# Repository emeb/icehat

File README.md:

# icehat

icehat is a small (Zero-sized) RPi hat which comprises a Lattice iCE40 Ultra
FPGA type ice5LP4K-SG48 along with voltage regulators, status LEDs and three
Digilent-style PMOD connectors.

This repository includes the full KiCAD board design source as well as C source
for an RPi user application which can configure the FPGA via GPIO and SPI ports
as well as communicate with a simple SPI slave hosted on the FPGA. Verilog
source for the FPGA test design is also included.

For more info on this project, please see the web page at:

http://ebrombaugh.studionebula.com/embedded/icehat/index.html

Credits: 

Portions of the KiCAD design are based on the RPi_Hat_Template from
xesscorp: https://github.com/xesscorp/RPi_Hat_Template

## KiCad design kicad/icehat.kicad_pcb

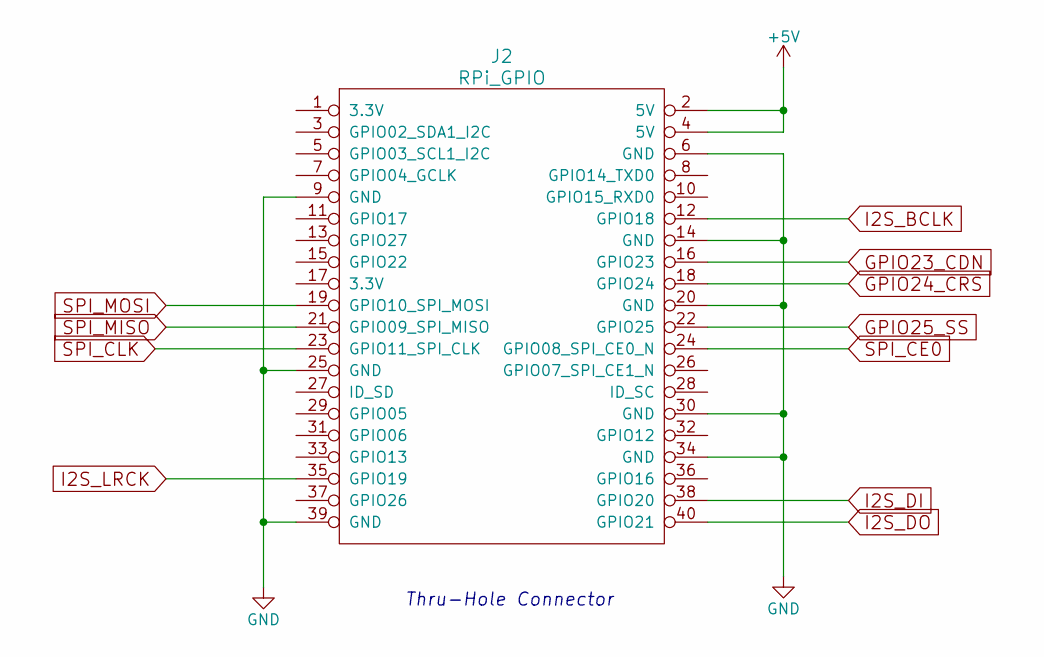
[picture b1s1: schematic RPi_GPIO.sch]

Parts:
J2: RPi_GPIO; Pin_Header_Straight_2x20

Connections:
+5V: J2.2 (5V), J2.4 (5V); also elsewhere on the board
GND: J2.6 (GND), J2.9 (GND), J2.14 (GND), J2.20 (GND), J2.25 (GND), J2.30 (GND), J2.34 (GND), J2.39 (GND); also elsewhere on the board
GPIO23_CDN: J2.16 (GPIO23); also elsewhere on the board
GPIO24_CRS: J2.18 (GPIO24); also elsewhere on the board
GPIO25_SS: J2.22 (GPIO25); also elsewhere on the board
I2S_BCLK: J2.12 (GPIO18); also elsewhere on the board
I2S_DI: J2.38 (GPIO20); also elsewhere on the board
I2S_DO: J2.40 (GPIO21); also elsewhere on the board
I2S_LRCK: J2.35 (GPIO19); also elsewhere on the board
SPI_CE0: J2.24 (GPIO08_SPI_CE0_N); also elsewhere on the board
SPI_CLK: J2.23 (GPIO11_SPI_CLK); also elsewhere on the board
SPI_MISO: J2.21 (GPIO09_SPI_MISO); also elsewhere on the board
SPI_MOSI: J2.19 (GPIO10_SPI_MOSI); also elsewhere on the board

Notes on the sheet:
Thru-Hole Connector

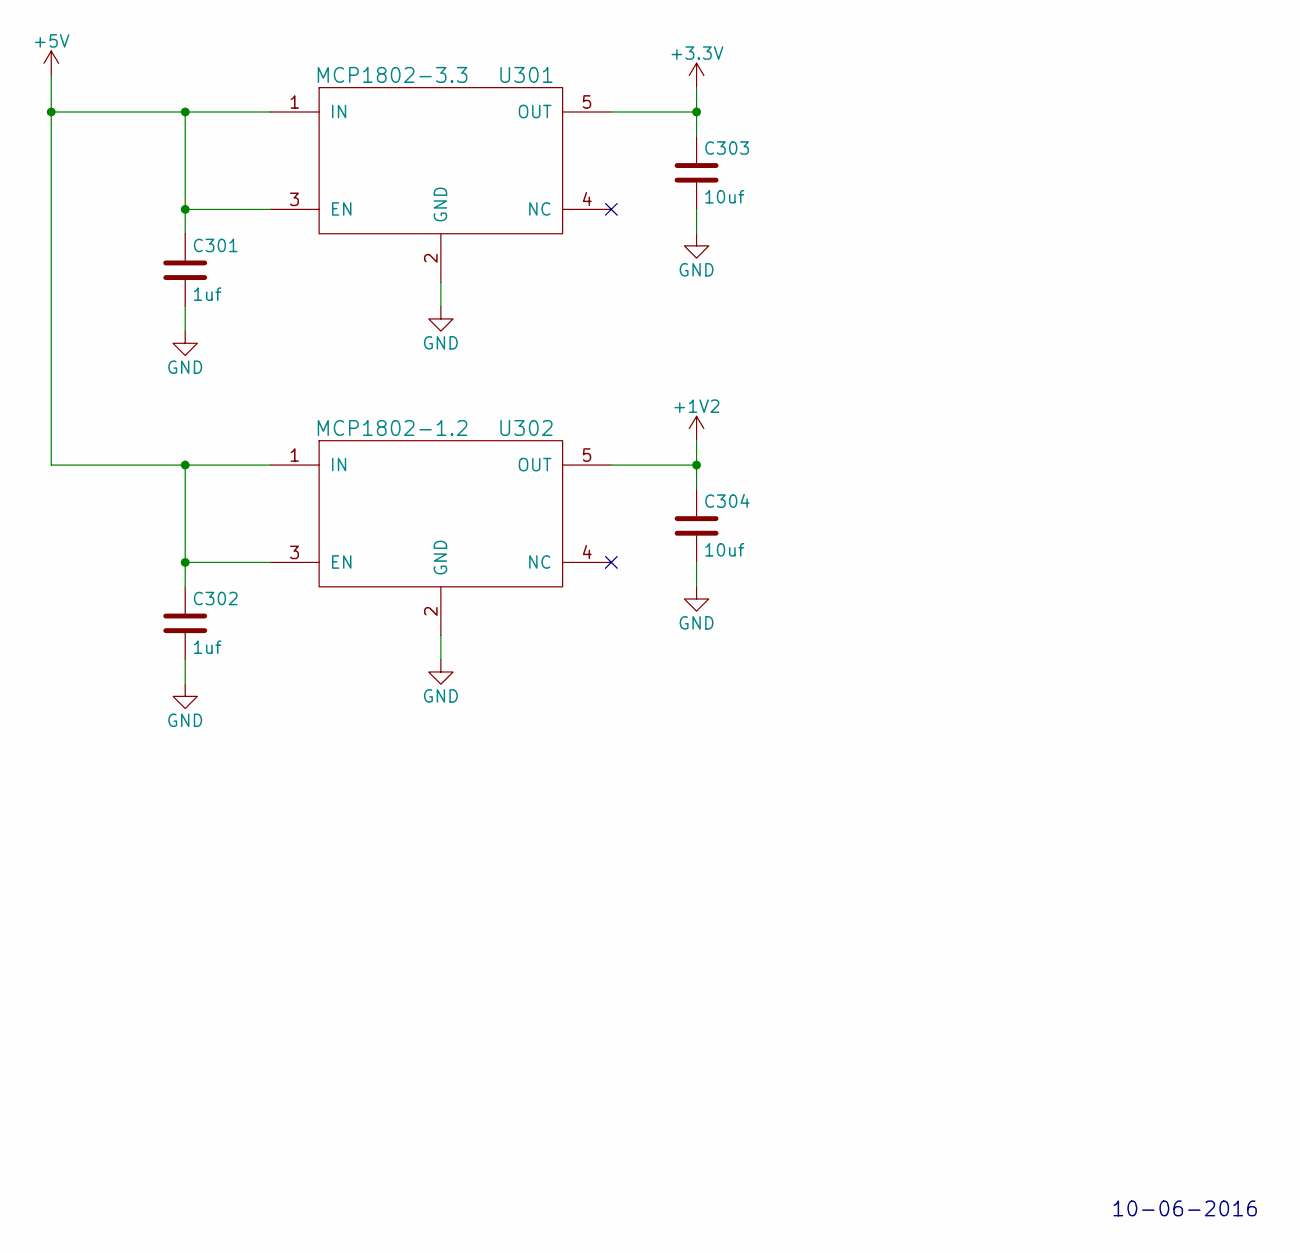
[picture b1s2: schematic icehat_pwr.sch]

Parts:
C301, C302: 1uf; C_0603
C303, C304: 10uf; C_0805
U301: MCP1802-3.3; SOT-23-5
U302: MCP1802-1.2; SOT-23-5

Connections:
+1V2: C304.1, U302.5 (OUT); also elsewhere on the board
+3V3: C303.1, U301.5 (OUT); also elsewhere on the board
+5V: C301.1, C302.1, U301.1 (IN), U301.3 (EN), U302.1 (IN), U302.3 (EN); also elsewhere on the board
GND: C301.2, C302.2, C303.2, C304.2, U301.2 (GND), U302.2 (GND); also elsewhere on the board

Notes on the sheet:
10-06-2016

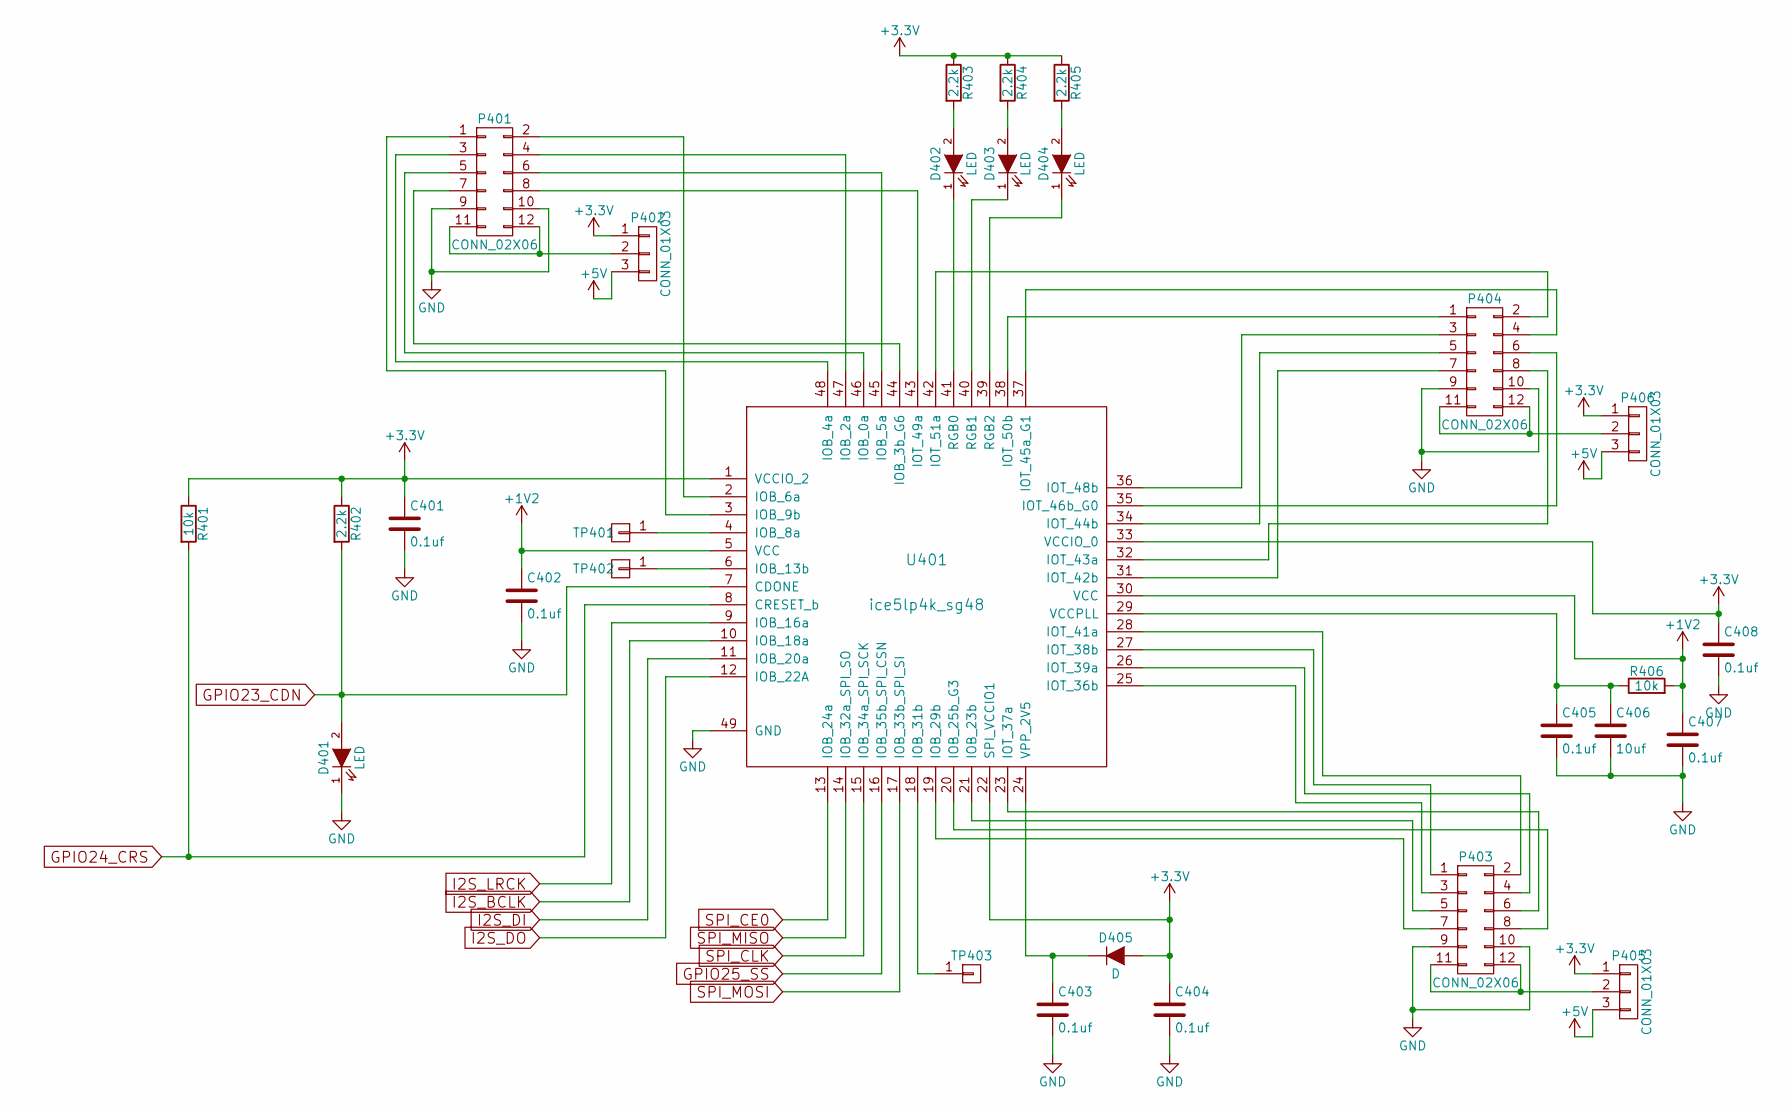
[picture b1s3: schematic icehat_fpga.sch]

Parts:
C401, C402, C403, C404, C405, C407, C408: 0.1uf; C_0603
C406: 10uf; R_0805
D401, D402, D403, D404: LED; LED_0805
D405: D; D_0603
P401, P403, P404: CONN_02X06; Pin_Header_Straight_2x06
P402, P405, P406: CONN_01X03; Pin_Header_Straight_1x03
R401, R406: 10k; R_0603
R402, R403, R404, R405: 2.2k; R_0603
TP401, TP402, TP403: CONN_01X01; PINTST
U401: ice5lp4k_sg48; QFN-48-1EP_7x7mm_Pitch0.5mm_DIY_PADS

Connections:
+1V2: C402.1, C407.1, R406.2, U401.5 (VCC), U401.30 (VCC); also elsewhere on the board
+3V3: C401.1, C404.1, C408.1, D405.2 (A), P402.1, P405.1, P406.1, R401.1, R402.1, R403.1, R404.1, R405.1, U401.1 (VCCIO_2), U401.22 (SPI_VCCIO1), U401.33 (VCCIO_0); also elsewhere on the board
+5V: P402.3, P405.3, P406.3; also elsewhere on the board
GND: C401.2, C402.2, C403.2, C404.2, C405.2, C406.2, C407.2, C408.2, D401.1 (K), P401.9, P401.10, P403.9, P403.10, P404.9, P404.10, U401.49 (GND); also elsewhere on the board
GPIO23_CDN: D401.2 (A), R402.2, U401.7 (CDONE); also elsewhere on the board
GPIO24_CRS: R401.2, U401.8 (CRESET_b); also elsewhere on the board
GPIO25_SS: U401.16 (IOB_35b_SPI_CSN); also elsewhere on the board
I2S_BCLK: U401.10 (IOB_18a); also elsewhere on the board
I2S_DI: U401.11 (IOB_20a); also elsewhere on the board
I2S_DO: U401.12 (IOB_22A); also elsewhere on the board
I2S_LRCK: U401.9 (IOB_16a); also elsewhere on the board
unnamed: C403.1, D405.1 (K), U401.24 (VPP_2V5)
unnamed: C405.1, C406.1, R406.1, U401.29 (VCCPLL)
unnamed: D402.1 (K), U401.41 (RGB0)
unnamed: D402.2 (A), R403.2
unnamed: D403.1 (K), U401.40 (RGB1)
unnamed: D403.2 (A), R404.2
unnamed: D404.1 (K), U401.39 (RGB2)
unnamed: D404.2 (A), R405.2
unnamed: P401.1, U401.3 (IOB_9b)
unnamed: P401.2, U401.2 (IOB_6a)
unnamed: P401.3, U401.48 (IOB_4a)
unnamed: P401.4, U401.47 (IOB_2a)
unnamed: P401.5, U401.46 (IOB_0a)
unnamed: P401.6, U401.45 (IOB_5a)
unnamed: P401.7, U401.44 (IOB_3b_G6)
unnamed: P401.8, U401.43 (IOT_49a)
unnamed: P401.11, P401.12, P402.2
unnamed: P403.1, U401.27 (IOT_38b)
unnamed: P403.2, U401.28 (IOT_41a)
unnamed: P403.3, U401.25 (IOT_36b)
unnamed: P403.4, U401.26 (IOT_39a)
unnamed: P403.5, U401.21 (IOB_23b)
unnamed: P403.6, U401.23 (IOT_37a)
unnamed: P403.7, U401.19 (IOB_29b)
unnamed: P403.8, U401.20 (IOB_25b_G3)
unnamed: P403.11, P403.12, P405.2
unnamed: P404.1, U401.38 (IOT_50b)
unnamed: P404.2, U401.42 (IOT_51a)
unnamed: P404.3, U401.36 (IOT_48b)
unnamed: P404.4, U401.37 (IOT_45a_G1)
unnamed: P404.5, U401.34 (IOT_44b)
unnamed: P404.6, U401.35 (IOT_46b_G0)
unnamed: P404.7, U401.31 (IOT_42b)
unnamed: P404.8, U401.32 (IOT_43a)
unnamed: P404.11, P404.12, P406.2
unnamed: TP401.1, U401.4 (IOB_8a)
unnamed: TP402.1, U401.6 (IOB_13b)
unnamed: TP403.1, U401.18 (IOB_31b)
SPI_CE0: U401.13 (IOB_24a); also elsewhere on the board
SPI_CLK: U401.15 (IOB_34a_SPI_SCK); also elsewhere on the board
SPI_MISO: U401.14 (IOB_32a_SPI_SO); also elsewhere on the board
SPI_MOSI: U401.17 (IOB_33b_SPI_SI); also elsewhere on the board

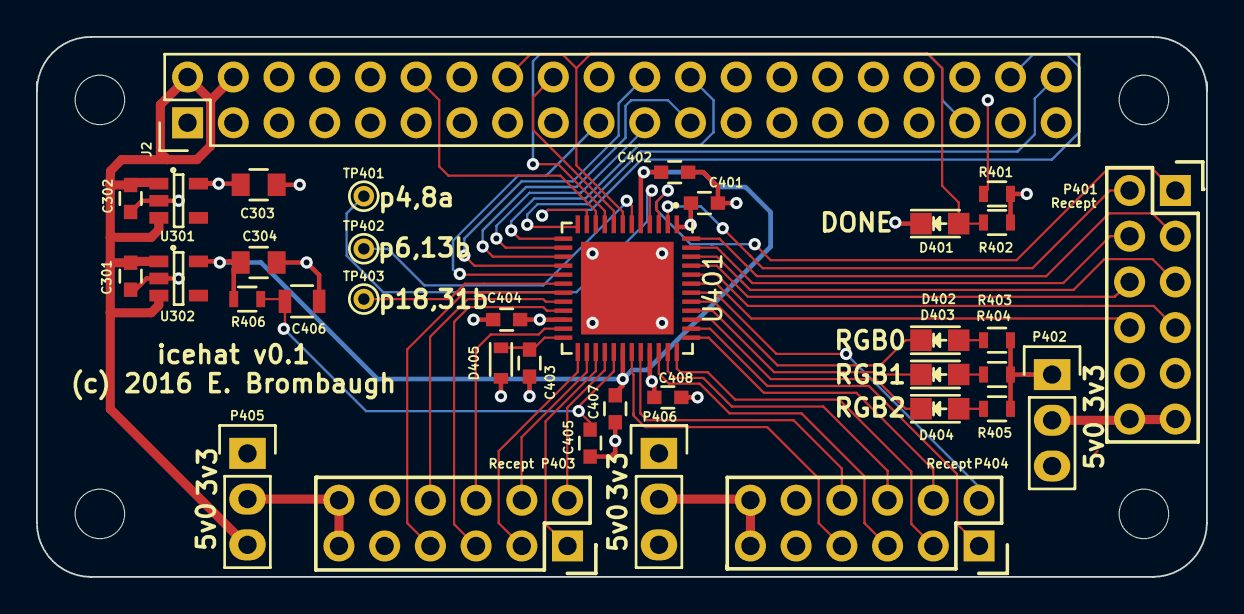
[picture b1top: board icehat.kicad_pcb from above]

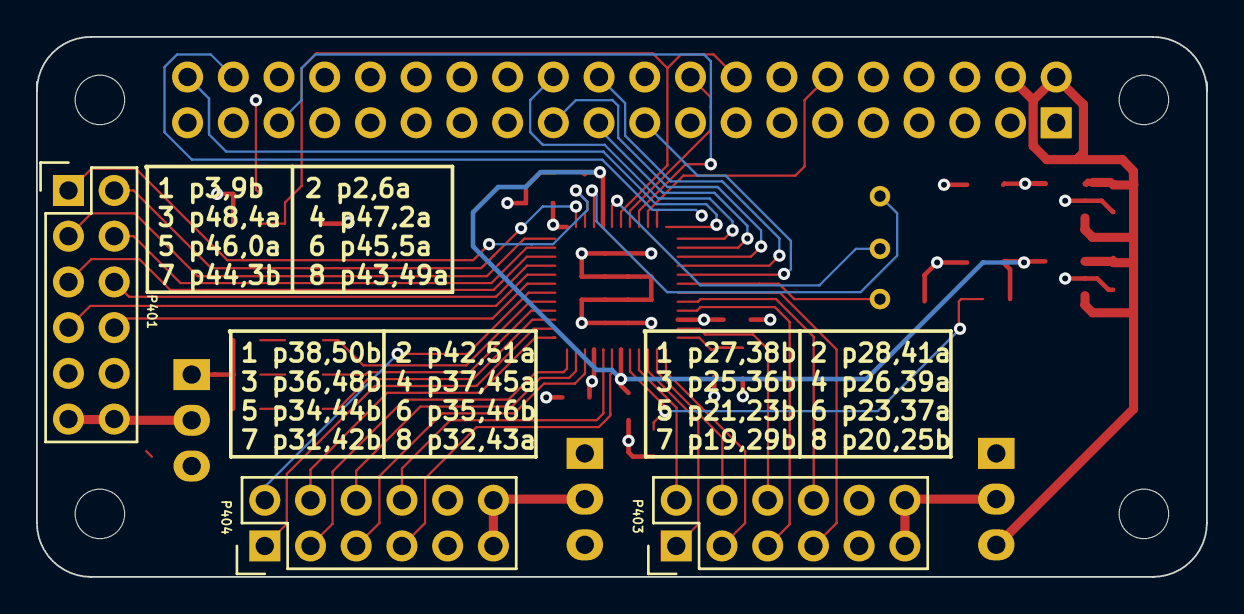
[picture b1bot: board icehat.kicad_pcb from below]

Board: 4 copper layers, 65.0 x 30.0 mm, 36 parts (3 on the bottom side), 53 nets.

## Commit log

2016-10-11 Initial commit of icehat RPi FPGA hat.
2016-10-11 Added docs and verilog
2016-10-11 Updated license
2016-10-11 Added board render and schematic
2016-11-02 Updated for icehat hardware testing
2017-01-13 Added back view
2017-01-13 Added link back to webpage
2017-01-26 Added BOM
2017-01-27 Fix some component values

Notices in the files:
kicad/icehat.kicad_pcb:
(c) 2016 E. Brombaugh
